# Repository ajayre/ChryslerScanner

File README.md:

# TJ Diag [![Badge License]][License]

![GUI CCD 01]

![GUI SCI 01]

![GUI EngineTools 01]

![GUI BootstrapTools 01]

<!----------------------------------------------------------------------------->

[Badge License]: https://img.shields.io/badge/License-GPLv3-blue.svg?style=for-the-badge
[GUI CCD 01]: https://chryslerccdsci.files.wordpress.com/2023/01/chryslerscanner_gui_ccd_01.png
[GUI SCI 01]: https://chryslerccdsci.files.wordpress.com/2023/01/chryslerscanner_gui_sci_01.png
[GUI EngineTools 01]: https://chryslerccdsci.files.wordpress.com/2023/01/chryslerscanner_gui_enginetools_01.png
[GUI BootstrapTools 01]: https://chryslerccdsci.files.wordpress.com/2023/01/chryslerscanner_gui_bootstraptools_01.png
[License]: LICENSE

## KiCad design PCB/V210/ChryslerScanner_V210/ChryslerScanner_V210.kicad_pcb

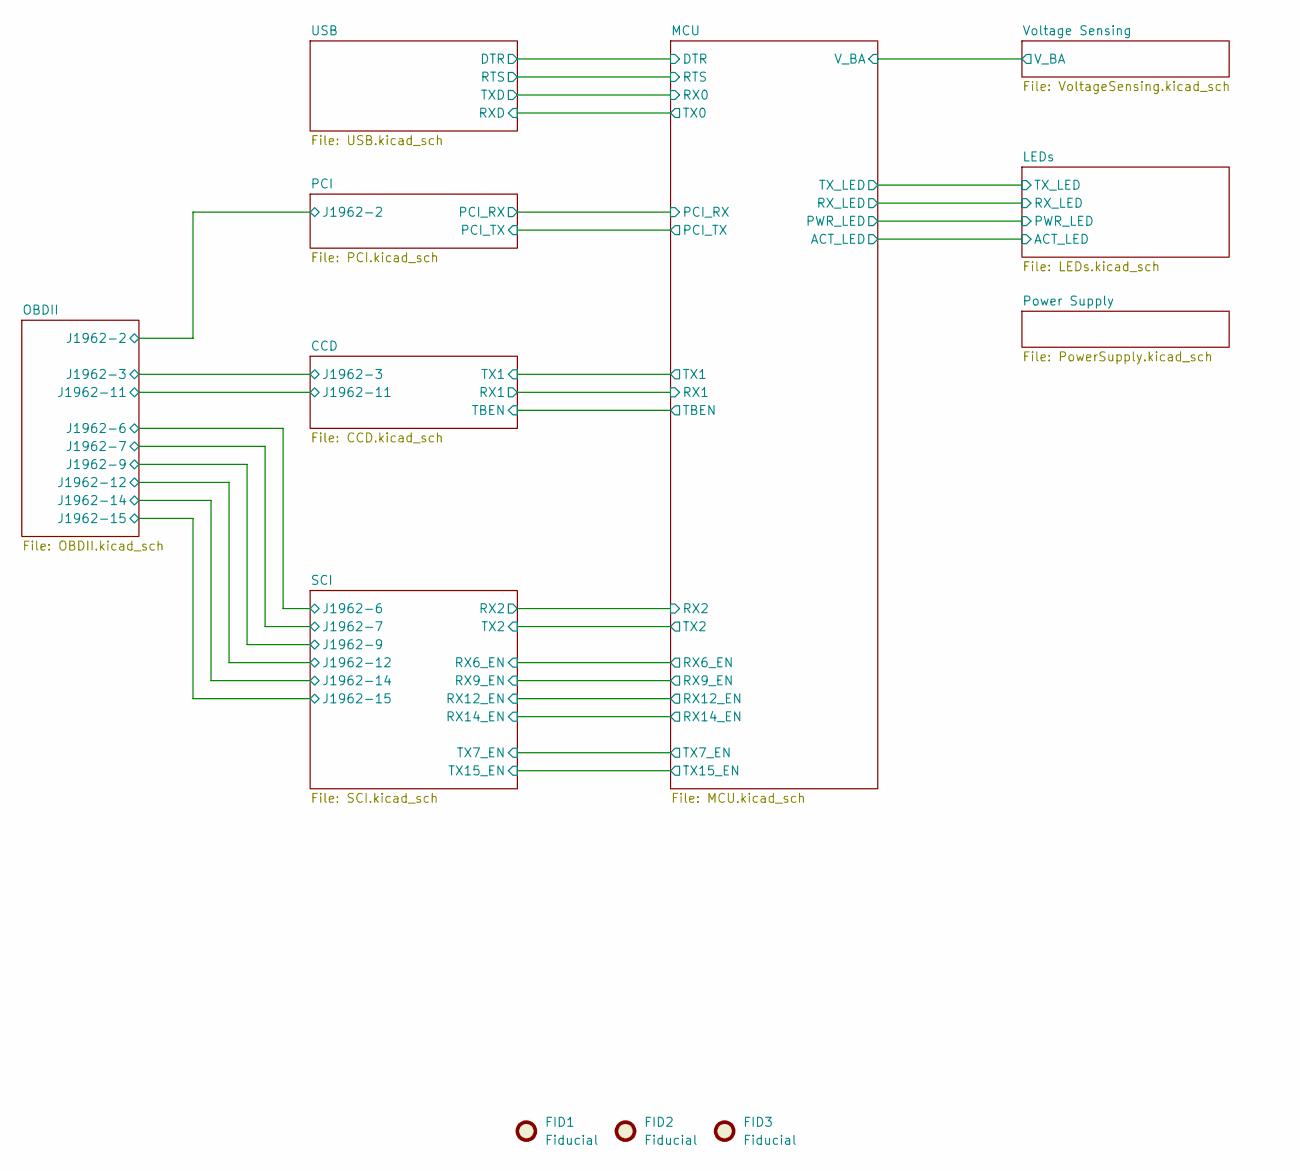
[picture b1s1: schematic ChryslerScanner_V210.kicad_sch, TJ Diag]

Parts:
FID1, FID2, FID3: Fiducial; Fiducial_0.5mm_Mask1mm

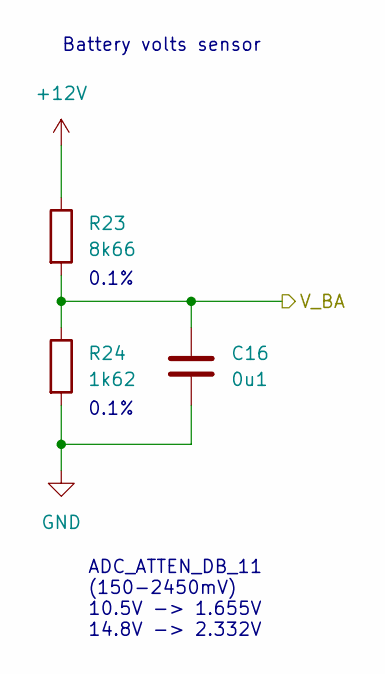
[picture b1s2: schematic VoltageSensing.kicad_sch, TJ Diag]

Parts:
C16: 0u1; C_0603_1608Metric
R23: 8k66; R_0603_1608Metric
R24: 1k62; R_0603_1608Metric

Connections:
/MCU/V_BA: C16.1, R23.2, R24.1; also elsewhere on the board
GND: C16.2, R24.2; also elsewhere on the board

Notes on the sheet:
ADC_ATTEN_DB_11 (150-2450mV) 10.5V -> 1.655V 14.8V -> 2.332V
0.1%
Battery volts sensor

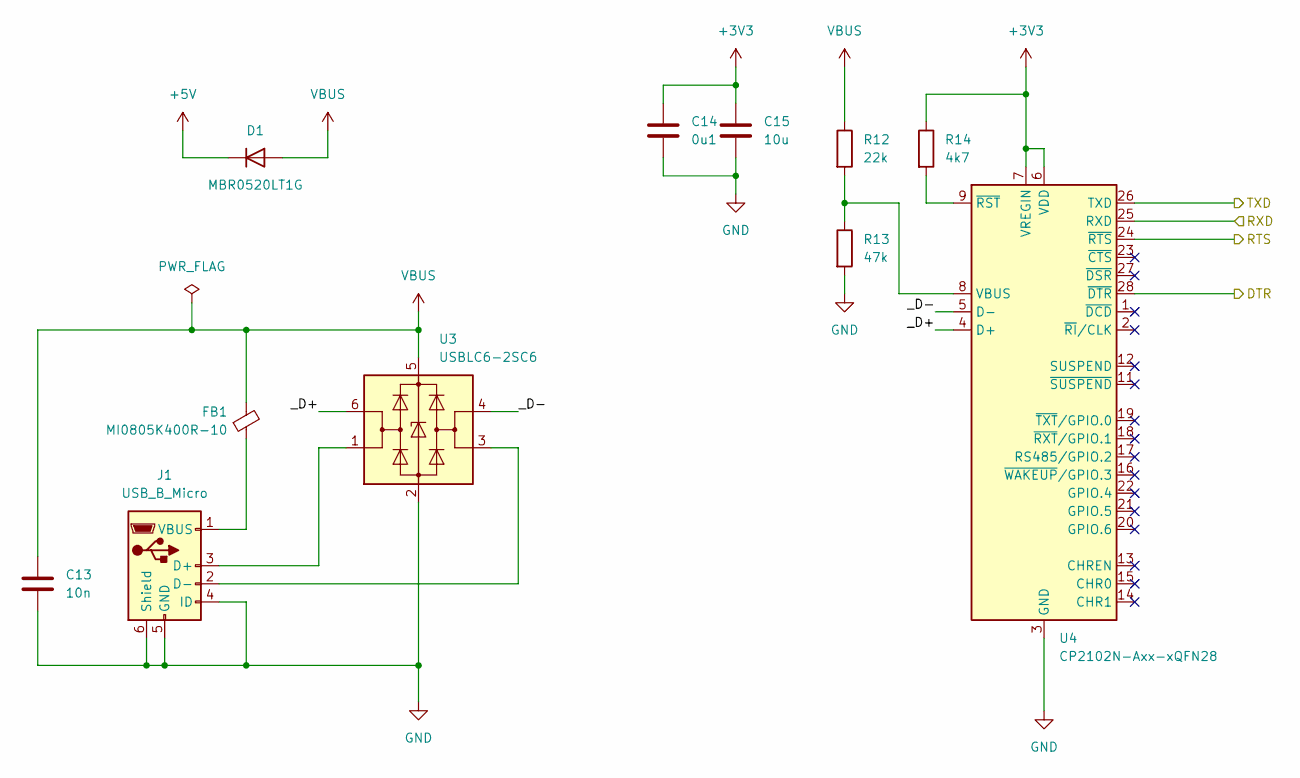
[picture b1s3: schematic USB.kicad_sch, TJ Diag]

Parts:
C13: 10n; C_0603_1608Metric
C14: 0u1; C_0603_1608Metric
C15: 10u; C_0603_1608Metric
D1: MBR0520LT1G; SOD-123
FB1: MI0805K400R-10; R_0805_2012Metric
J1: USB_B_Micro; USB_Micro-B_Amphenol_10103594-0001LF_Horizontal
R12: 22k; R_0603_1608Metric
R13: 47k; R_0603_1608Metric
R14: 4k7; R_0603_1608Metric
U3: USBLC6-2SC6; SOT-23-6
U4: CP2102N-Axx-xQFN28; QFN-28-1EP_5x5mm_P0.5mm_EP3.35x3.35mm

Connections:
+3V3: C14.1, C15.1, R14.1, U4.6 (VDD), U4.7 (VREGIN); also elsewhere on the board
+5V: D1.1 (K); also elsewhere on the board
/MCU/DTR: U4.28 (~DTR); also elsewhere on the board
/MCU/RTS: U4.24 (~RTS); also elsewhere on the board
/MCU/RX0: U4.26 (TXD); also elsewhere on the board
/MCU/TX0: U4.25 (RXD); also elsewhere on the board
/USB/_D+: U3.6 (I/O1), U4.4 (D+)
/USB/_D-: U3.4 (I/O2), U4.5 (D-)
GND: C13.2, C14.2, C15.2, J1.4 (ID), J1.5 (GND), J1.6 (Shield), R13.2, U3.2 (GND), U4.3 (GND), U4.29 (GND); also elsewhere on the board
unnamed: FB1.1, J1.1 (VBUS)
unnamed: J1.2 (D-), U3.3 (I/O2)
unnamed: J1.3 (D+), U3.1 (I/O1)
unnamed: R12.2, R13.1, U4.8 (VBUS)
unnamed: R14.2, U4.9 (~RST)
VBUS: C13.1, D1.2 (A), FB1.2, R12.1, U3.5 (VBUS)

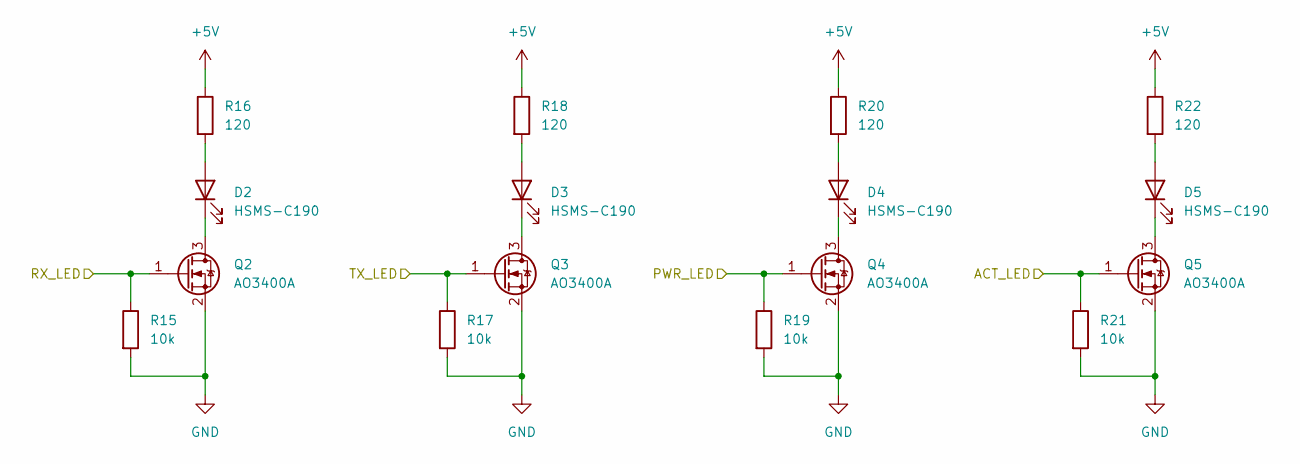
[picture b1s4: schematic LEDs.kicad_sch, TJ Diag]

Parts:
D2, D3, D4, D5: HSMS-C190; LED_0603_1608Metric
Q2, Q3, Q4, Q5: AO3400A; SOT-23
R15, R17, R19, R21: 10k; R_0603_1608Metric
R16, R18, R20, R22: 120; R_0603_1608Metric

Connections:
+5V: R16.1, R18.1, R20.1, R22.1; also elsewhere on the board
/LEDs/ACT_LED: Q5.1 (G), R21.1; also elsewhere on the board
/LEDs/PWR_LED: Q4.1 (G), R19.1; also elsewhere on the board
/LEDs/RX_LED: Q2.1 (G), R15.1; also elsewhere on the board
/LEDs/TX_LED: Q3.1 (G), R17.1; also elsewhere on the board
GND: Q2.2 (S), Q3.2 (S), Q4.2 (S), Q5.2 (S), R15.2, R17.2, R19.2, R21.2; also elsewhere on the board
unnamed: D2.1 (K), Q2.3 (D)
unnamed: D2.2 (A), R16.2
unnamed: D3.1 (K), Q3.3 (D)
unnamed: D3.2 (A), R18.2
unnamed: D4.1 (K), Q4.3 (D)
unnamed: D4.2 (A), R20.2
unnamed: D5.1 (K), Q5.3 (D)
unnamed: D5.2 (A), R22.2

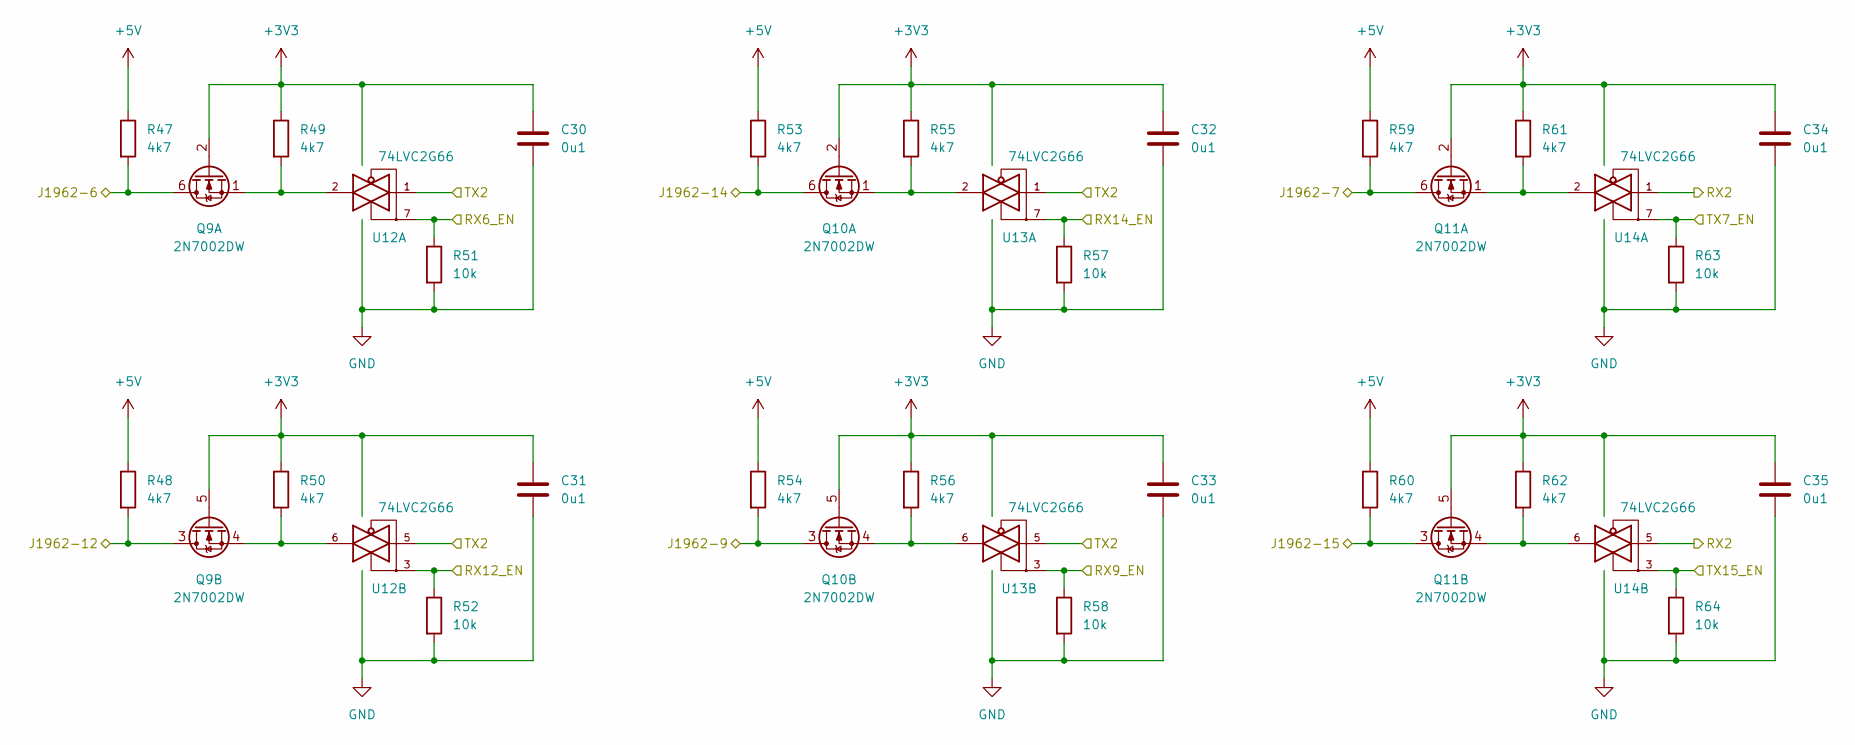
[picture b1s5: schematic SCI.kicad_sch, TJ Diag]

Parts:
C30, C31, C32, C33, C34, C35: 0u1; C_0603_1608Metric
Q9, Q10, Q11: 2N7002DW; SOT-363_SC-70-6
R47, R48, R49, R50, R53, R54, R55, R56, R59, R60, R61, R62: 4k7; R_0603_1608Metric
R51, R52, R57, R58, R63, R64: 10k; R_0603_1608Metric
U12, U13, U14: 74LVC2G66; TSSOP-8_3x3mm_P0.65mm

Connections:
+3V3: C30.1, C31.1, C32.1, C33.1, C34.1, C35.1, Q9.2 (G), Q9.5 (G), Q10.2 (G), Q10.5 (G), Q11.2 (G), Q11.5 (G), R49.1, R50.1, R55.1, R56.1, R61.1, R62.1, U12.8 (VCC), U13.8 (VCC), U14.8 (VCC); also elsewhere on the board
+5V: R47.1, R48.1, R53.1, R54.1, R59.1, R60.1; also elsewhere on the board
/MCU/RX2: U14.1, U14.5; also elsewhere on the board
/MCU/RX6_EN: R51.1, U12.7; also elsewhere on the board
/MCU/RX9_EN: R58.1, U13.3; also elsewhere on the board
/MCU/RX12_EN: R52.1, U12.3; also elsewhere on the board
/MCU/RX14_EN: R57.1, U13.7; also elsewhere on the board
/MCU/TX2: U12.1, U12.5, U13.1, U13.5; also elsewhere on the board
/MCU/TX7_EN: R63.1, U14.7; also elsewhere on the board
/MCU/TX15_EN: R64.1, U14.3; also elsewhere on the board
/OBDII/SCI_PCM_RX_A-6: Q9.6 (D), R47.2; also elsewhere on the board
/OBDII/SCI_PCM_RX_B-12: Q9.3 (D), R48.2; also elsewhere on the board
/OBDII/SCI_PCM_TX_AB_TCM_TX_A-7: Q11.6 (D), R59.2; also elsewhere on the board
/OBDII/SCI_TCM_RX_A-14: Q10.6 (D), R53.2; also elsewhere on the board
/OBDII/SCI_TCM_RX_B-9: Q10.3 (D), R54.2; also elsewhere on the board
/OBDII/SCI_TCM_TX_B-15: Q11.3 (D), R60.2; also elsewhere on the board
GND: C30.2, C31.2, C32.2, C33.2, C34.2, C35.2, R51.2, R52.2, R57.2, R58.2, R63.2, R64.2, U12.4 (GND), U13.4 (GND), U14.4 (GND); also elsewhere on the board
unnamed: Q9.1 (S), R49.2, U12.2
unnamed: Q9.4 (S), R50.2, U12.6
unnamed: Q10.1 (S), R55.2, U13.2
unnamed: Q10.4 (S), R56.2, U13.6
unnamed: Q11.1 (S), R61.2, U14.2
unnamed: Q11.4 (S), R62.2, U14.6

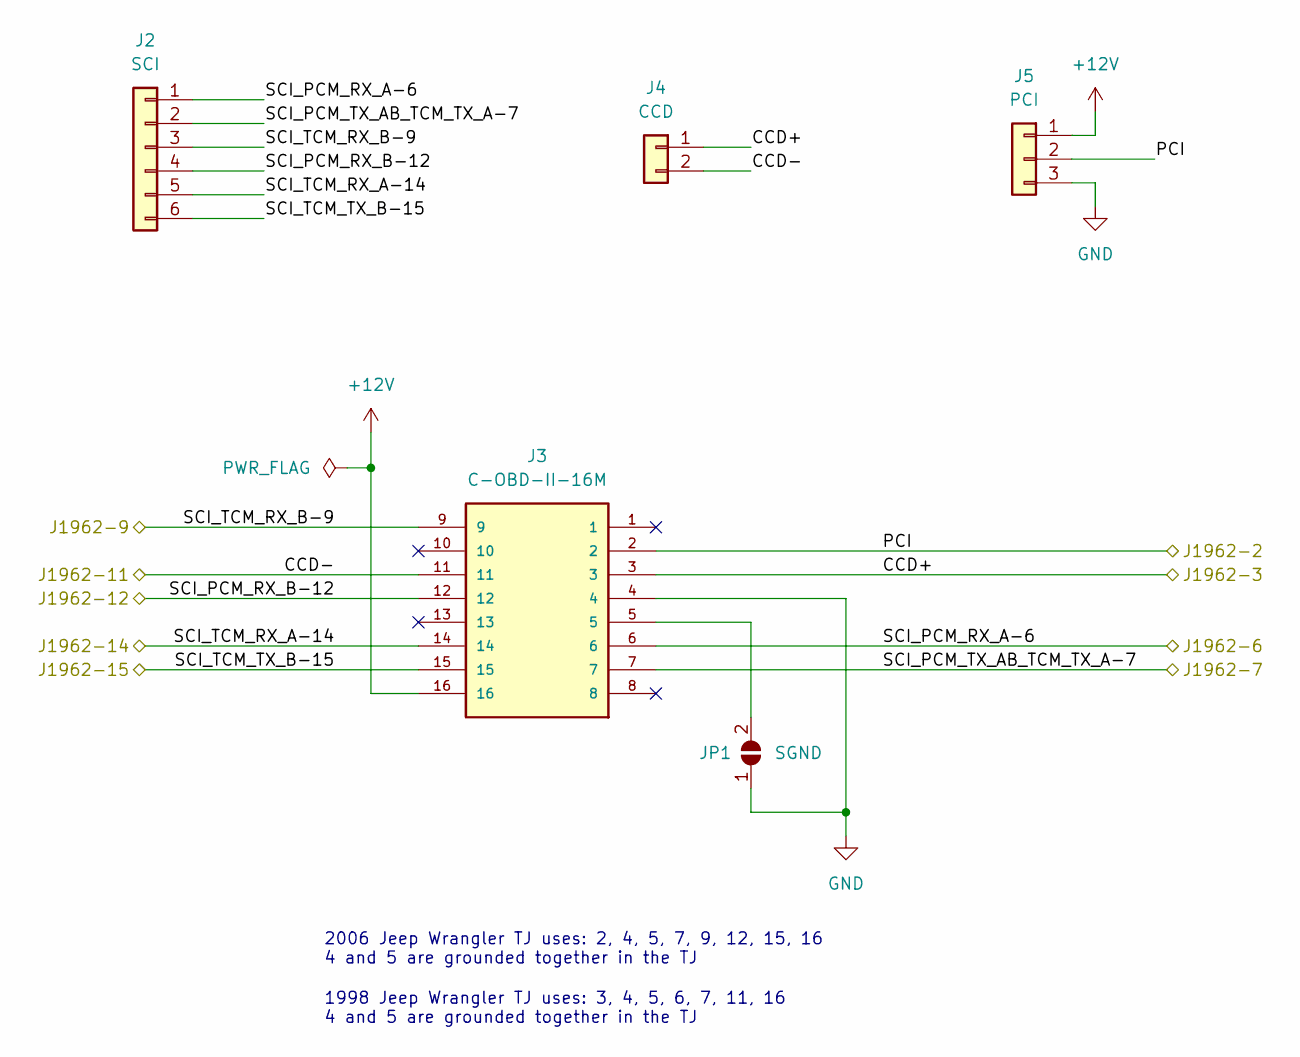
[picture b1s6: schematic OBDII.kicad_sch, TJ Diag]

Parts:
J2: SCI; PinHeader_1x06_P2.54mm_Vertical
J3: C-OBD-II-16M; COMTECH_C-OBD-II-16M; PARTREV A
J4: CCD; PinHeader_1x02_P2.54mm_Vertical
J5: PCI; PinHeader_1x03_P2.54mm_Vertical
JP1: SGND; SolderJumper-2_P1.3mm_Open_TrianglePad1.0x1.5mm

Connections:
/OBDII/CCD+: J3.3, J4.1; also elsewhere on the board
/OBDII/CCD-: J3.11, J4.2; also elsewhere on the board
/OBDII/PCI: J3.2, J5.2; also elsewhere on the board
/OBDII/SCI_PCM_RX_A-6: J2.1, J3.6; also elsewhere on the board
/OBDII/SCI_PCM_RX_B-12: J2.4, J3.12; also elsewhere on the board
/OBDII/SCI_PCM_TX_AB_TCM_TX_A-7: J2.2, J3.7; also elsewhere on the board
/OBDII/SCI_TCM_RX_A-14: J2.5, J3.14; also elsewhere on the board
/OBDII/SCI_TCM_RX_B-9: J2.3, J3.9; also elsewhere on the board
/OBDII/SCI_TCM_TX_B-15: J2.6, J3.15; also elsewhere on the board
GND: J3.4, J5.3, JP1.1 (A); also elsewhere on the board
unnamed: J3.5, JP1.2 (B)

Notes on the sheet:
2006 Jeep Wrangler TJ uses: 2, 4, 5, 7, 9, 12, 15, 16 4 and 5 are grounded together in the TJ
1998 Jeep Wrangler TJ uses: 3, 4, 5, 6, 7, 11, 16 4 and 5 are grounded together in the TJ

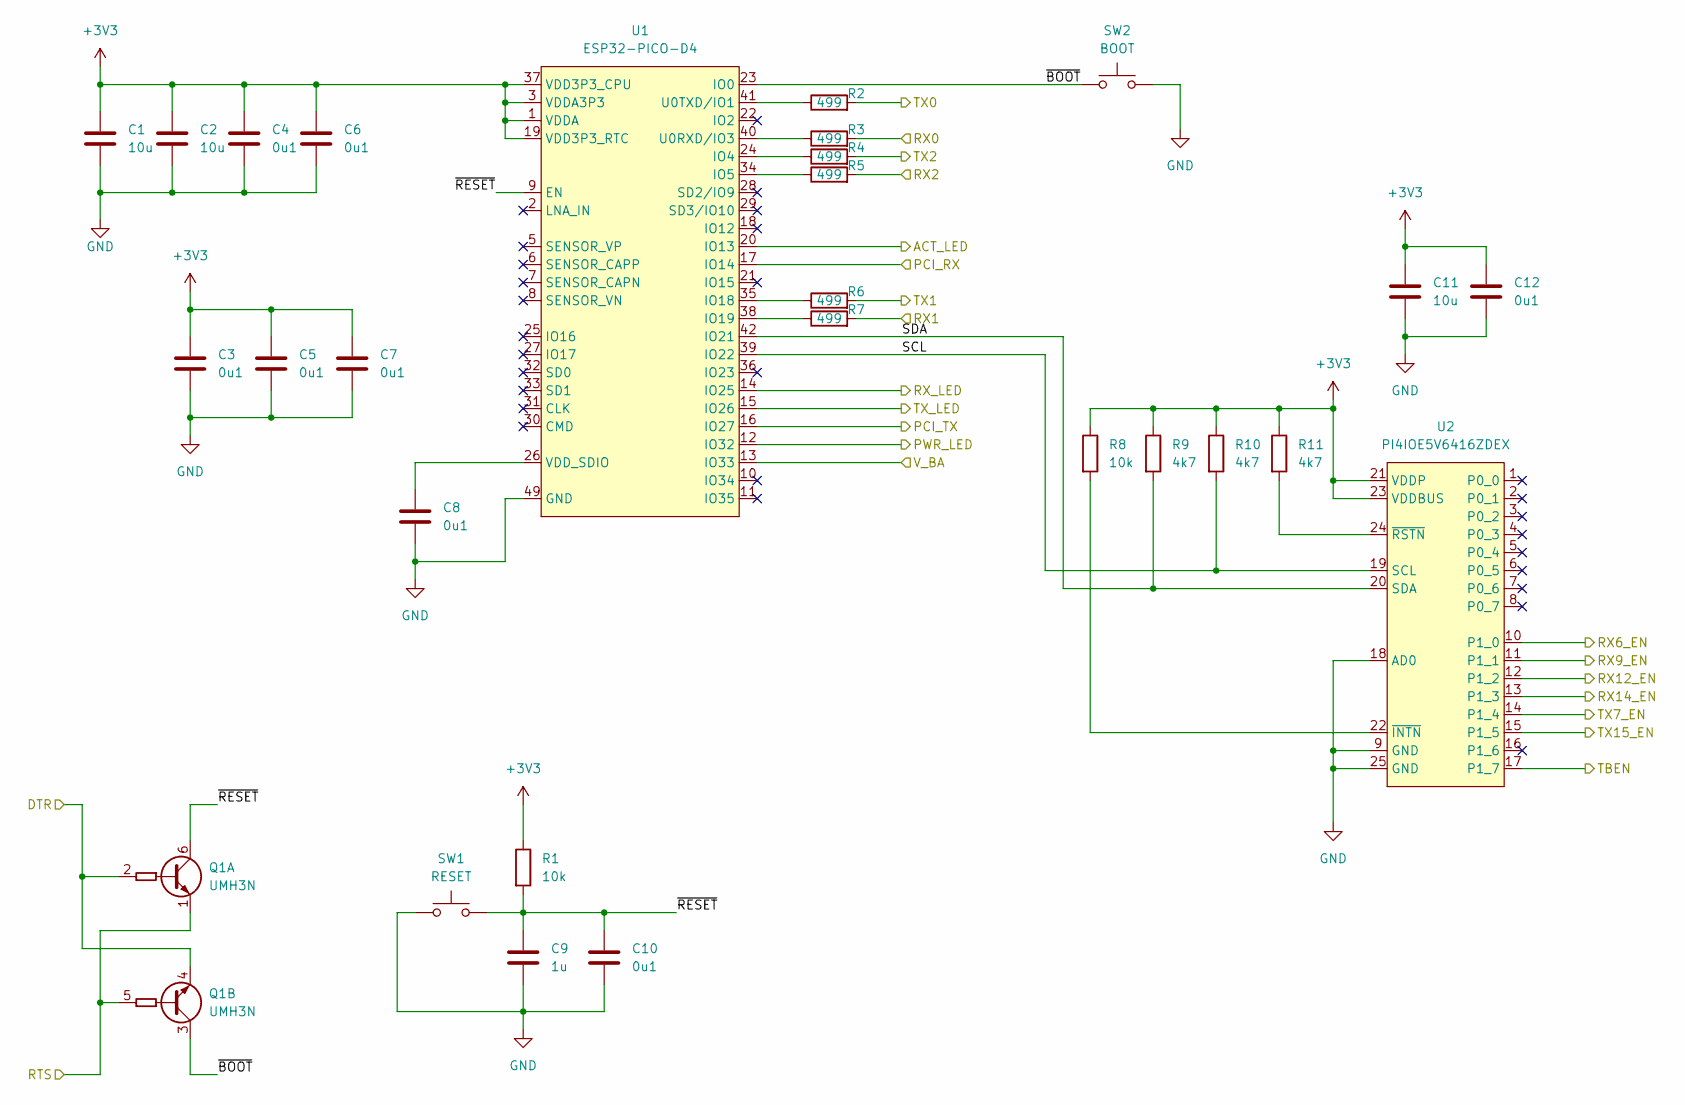
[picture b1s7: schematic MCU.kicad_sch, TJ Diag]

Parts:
C1, C2, C11: 10u; C_0603_1608Metric
C3, C4, C5, C6, C7, C8, C10, C12: 0u1; C_0603_1608Metric
C9: 1u; C_0603_1608Metric
Q1: UMH3N; SOT-363_SC-70-6
R1, R8: 10k; R_0603_1608Metric
R2, R3, R4, R5, R6, R7: 499; R_0603_1608Metric
R9, R10, R11: 4k7; R_0603_1608Metric
SW1: RESET; TL6330 Tactile Switch
SW2: BOOT; TL6330 Tactile Switch
U1: ESP32-PICO-D4; QFN-48-1EP_7x7mm_P0.5mm_EP5.15x5.15mm_ThermalVias
U2: PI4IOE5V6416ZDEX; QFN-24-1EP_4x4mm_P0.5mm_EP2.15x2.15mm_ThermalVias

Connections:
+3V3: C1.1, C2.1, C3.1, C4.1, C5.1, C6.1, C7.1, C11.1, C12.1, R1.1, R8.1, R9.1, R10.1, R11.1, U1.1 (VDDA), U1.3 (VDDA3P3), U1.4 (VDDA3P3), U1.19 (VDD3P3_RTC), U1.37 (VDD3P3_CPU), U1.43 (VDDA), U1.46 (VDDA), U2.21 (VDDP), U2.23 (VDDBUS); also elsewhere on the board
/CCD/RX1: R7.2; also elsewhere on the board
/CCD/TBEN: U2.17 (P1_7); also elsewhere on the board
/CCD/TX1: R6.2; also elsewhere on the board
/LEDs/ACT_LED: U1.20 (IO13); also elsewhere on the board
/LEDs/PWR_LED: U1.12 (IO32); also elsewhere on the board
/LEDs/RX_LED: U1.14 (IO25); also elsewhere on the board
/LEDs/TX_LED: U1.15 (IO26); also elsewhere on the board
/MCU/DTR: Q1.2 (B1), Q1.4 (E2); also elsewhere on the board
/MCU/PCI_RX: U1.17 (IO14); also elsewhere on the board
/MCU/PCI_TX: U1.16 (IO27); also elsewhere on the board
/MCU/RTS: Q1.1 (E1), Q1.5 (B2); also elsewhere on the board
/MCU/RX0: R3.2; also elsewhere on the board
/MCU/RX2: R5.2; also elsewhere on the board
/MCU/RX6_EN: U2.10 (P1_0); also elsewhere on the board
/MCU/RX9_EN: U2.11 (P1_1); also elsewhere on the board
/MCU/RX12_EN: U2.12 (P1_2); also elsewhere on the board
/MCU/RX14_EN: U2.13 (P1_3); also elsewhere on the board
/MCU/SCL: R10.2, U1.39 (IO22), U2.19 (SCL)
/MCU/SDA: R9.2, U1.42 (IO21), U2.20 (SDA)
/MCU/TX0: R2.2; also elsewhere on the board
/MCU/TX2: R4.2; also elsewhere on the board
/MCU/TX7_EN: U2.14 (P1_4); also elsewhere on the board
/MCU/TX15_EN: U2.15 (P1_5); also elsewhere on the board
/MCU/V_BA: U1.13 (IO33); also elsewhere on the board
/MCU/~BOOT: Q1.3 (C2), SW2.1, U1.23 (IO0)
/MCU/~RESET: C9.1, C10.1, Q1.6 (C1), R1.2, SW1.2, U1.9 (EN)
GND: C1.2, C2.2, C3.2, C4.2, C5.2, C6.2, C7.2, C8.2, C9.2, C10.2, C11.2, C12.2, SW1.1, SW2.2, U1.49 (GND), U2.9 (GND), U2.18 (AD0), U2.25 (GND); also elsewhere on the board
unnamed: C8.1, U1.26 (VDD_SDIO)
unnamed: R2.1, U1.41 (U0TXD/IO1)
unnamed: R3.1, U1.40 (U0RXD/IO3)
unnamed: R4.1, U1.24 (IO4)
unnamed: R5.1, U1.34 (IO5)
unnamed: R6.1, U1.35 (IO18)
unnamed: R7.1, U1.38 (IO19)
unnamed: R8.2, U2.22 (~INTN)
unnamed: R11.2, U2.24 (~RSTN)

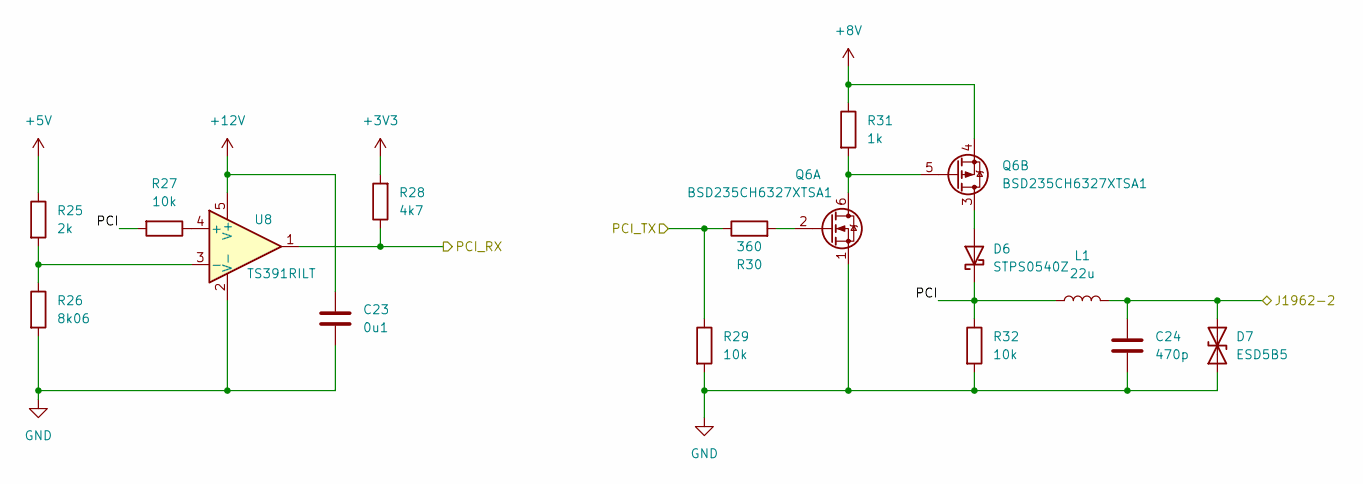
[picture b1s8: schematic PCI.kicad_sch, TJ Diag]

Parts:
C23: 0u1; C_0603_1608Metric
C24: 470p; C_0603_1608Metric
D6: STPS0540Z; SOD-123
D7: ESD5B5; D_SOD-523
L1: 22u; L_0805_2012Metric
Q6: BSD235CH6327XTSA1; SOT-363_SC-70-6
R25: 2k; R_0603_1608Metric
R26: 8k06; R_0603_1608Metric
R27, R29, R32: 10k; R_0603_1608Metric
R28: 4k7; R_0603_1608Metric
R30: 360; R_0603_1608Metric
R31: 1k; R_0603_1608Metric
U8: TS391RILT; SOT-23-5

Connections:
+3V3: R28.2; also elsewhere on the board
+5V: R25.1; also elsewhere on the board
+8V: Q6.4 (1), R31.1; also elsewhere on the board
/MCU/PCI_RX: R28.1, U8.1; also elsewhere on the board
/MCU/PCI_TX: R29.1, R30.1; also elsewhere on the board
/OBDII/PCI: C24.1, D7.2 (A2), L1.2; also elsewhere on the board
/PCI/PCI: D6.1 (K), L1.1, R27.2, R32.1
GND: C23.2, C24.2, D7.1 (A1), Q6.1 (S), R26.2, R29.2, R32.2, U8.2 (V-); also elsewhere on the board
unnamed: D6.2 (A), Q6.3 (D)
unnamed: Q6.2 (G), R30.2
unnamed: Q6.5 (G), Q6.6 (D), R31.2
unnamed: R25.2, R26.1, U8.3 (-)
unnamed: R27.1, U8.4 (+)

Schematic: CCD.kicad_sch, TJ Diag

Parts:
C25, C26, C29: 0u1; C_0603_1608Metric
C27, C28: 22n; C_0603_1608Metric
D8, D9: ESD5B5; D_SOD-523
D10, D11: 15V; D_SOD-323
Q7: BSD235CH6327XTSA1; SOT-363_SC-70-6
Q8: IRF7324; SOIC-8_3.9x4.9mm_P1.27mm
R33, R46: 4k7; R_0603_1608Metric
R34, R35: 100; R_0603_1608Metric
R36, R37: 360; R_0603_1608Metric
R38, R40: 13k; R_0603_1608Metric
R39: 120; R_0603_1608Metric
R41, R44, R45: 10k; R_0603_1608Metric
R42, R43: 10; R_0603_1608Metric
U9, U10: SN74LVC1G14DBV; SOT-23-5
U11: TS391RILT; SOT-23-5

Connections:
+3V3: R33.1, R46.1; also elsewhere on the board
+5V: C25.1, C26.1, C29.1, Q7.4 (1), R38.1, U9.5 (VCC), U10.5 (VCC), U11.5 (V+); also elsewhere on the board
/CCD/CCD+: C28.1, D11.1 (K), R36.1, R43.1, R45.2
/CCD/CCD-: C27.1, D10.1 (K), R37.1, R42.1, R44.2
/CCD/RX1: R46.2, U11.1; also elsewhere on the board
/CCD/TBEN: Q8.2 (G1), Q8.4 (G2), R41.1; also elsewhere on the board
/CCD/TX1: R33.2, U9.2, U10.2; also elsewhere on the board
/OBDII/CCD+: D9.2 (A2), Q8.5 (D2), Q8.6 (D2), R43.2; also elsewhere on the board
/OBDII/CCD-: D8.2 (A2), Q8.7 (D1), Q8.8 (D1), R42.2; also elsewhere on the board
GND: C25.2, C26.2, C27.2, C28.2, C29.2, D8.1 (A1), D9.1 (A1), D10.2 (A), D11.2 (A), Q7.1 (S), R40.2, R41.2, U9.3 (GND), U10.3 (GND), U11.2 (V-); also elsewhere on the board
unnamed: Q7.2 (G), R35.1
unnamed: Q7.3 (D), R36.2
unnamed: Q7.5 (G), R34.1
unnamed: Q7.6 (D), R37.2
unnamed: Q8.1 (S1), R38.2, R39.1
unnamed: Q8.3 (S2), R39.2, R40.1
unnamed: R34.2, U9.4
unnamed: R35.2, U10.4
unnamed: R44.1, U11.4 (+)
unnamed: R45.1, U11.3 (-)

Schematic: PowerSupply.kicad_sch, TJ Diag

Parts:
C17, C21, C22: 2u2; C_0603_1608Metric
C18: 0u33; C_0603_1608Metric
C19, C20: 1u; C_0603_1608Metric
U5: NCV7808BDTRKG; TO-252-2
U6: TLV76150DCYR; SOT-223-3_TabPin2
U7: TLV76133DCYR; SOT-223-3_TabPin2

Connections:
+3V3: C22.1, U7.2 (VO); also elsewhere on the board
+5V: C21.1, U6.2 (VO); also elsewhere on the board
+8V: C17.1, U5.3 (OUT); also elsewhere on the board
GND: C17.2, C18.2, C19.2, C20.2, C21.2, C22.2, U5.2 (GND), U6.1 (GND), U7.1 (GND); also elsewhere on the board

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
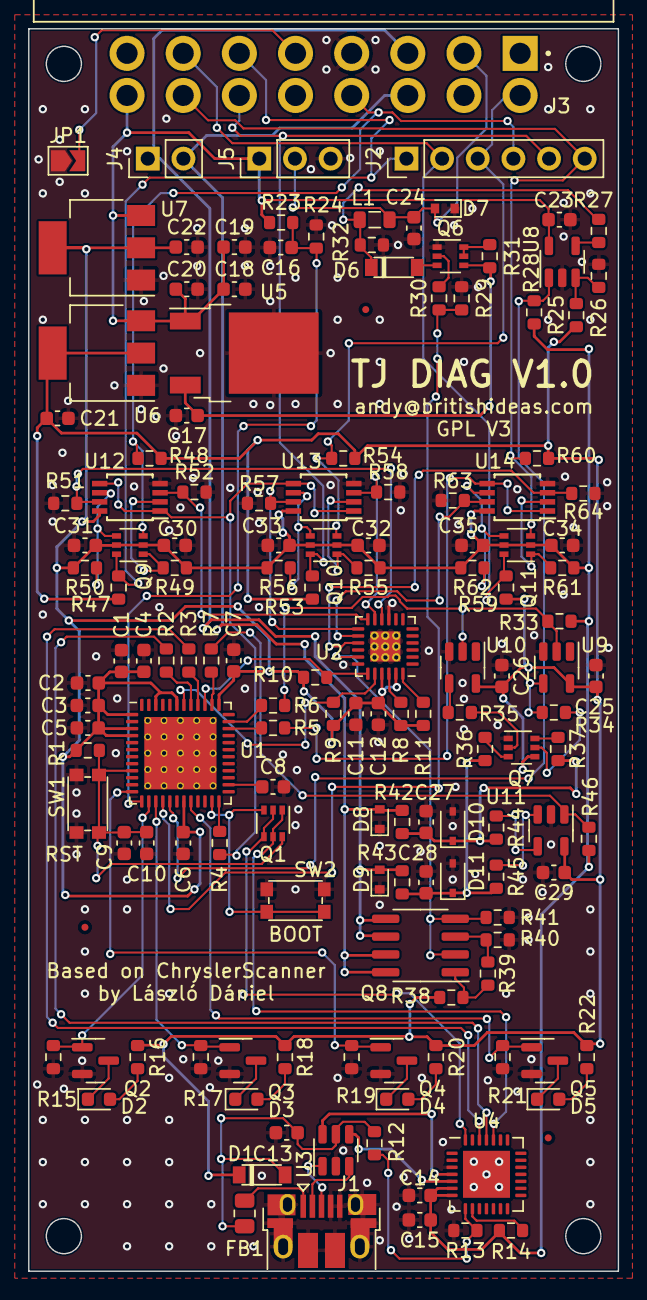
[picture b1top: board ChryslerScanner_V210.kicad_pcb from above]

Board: 2 copper layers, 42.0 x 88.5 mm, 148 parts (0 on the bottom side), 90 nets.

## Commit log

2023-06-25 Working on re-creating schematic. Added 10nF capacitor and ferrite bead near USB connector.
2023-06-25 Added schematic symbol library needed for V210 schematic.
2023-06-25 Added power supplies. Removed CCD.
2023-06-25 Completed schematic.
2023-07-02 Added file that was deleted by mistake.
2023-07-02 Updated schematic
2023-07-07 Working on power supplies. Added datasheets.
2023-07-07 Added OBD-II connector.
2023-07-09 Added CCD back in - needed for early TJs.
2023-07-19 Final component assignments.
2023-09-10 Working on PCB layout. Deleted old versions.
2023-09-12 Working on PCB layout.
2023-09-13 Added Jeep TJ silhouette to bottom of board.
2023-09-13 Added step model.
2023-09-13 Renamed folder.
2023-09-14 Added Alibre Design files for PCB and started work on case.
2023-09-14 Renamed folder
2023-09-14 Renamed KiCAD project.
2023-09-14 Deleted old schematics
2023-09-15 Completed case design.
2023-09-15 Cropped renders.
2023-09-22 Reformatted schematic pages to US Letter. Generated schematic PDF.

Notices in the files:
PCB/V1/ChryslerScanner_V210/CCD.kicad_sch:
GPL V3 LICENSE
